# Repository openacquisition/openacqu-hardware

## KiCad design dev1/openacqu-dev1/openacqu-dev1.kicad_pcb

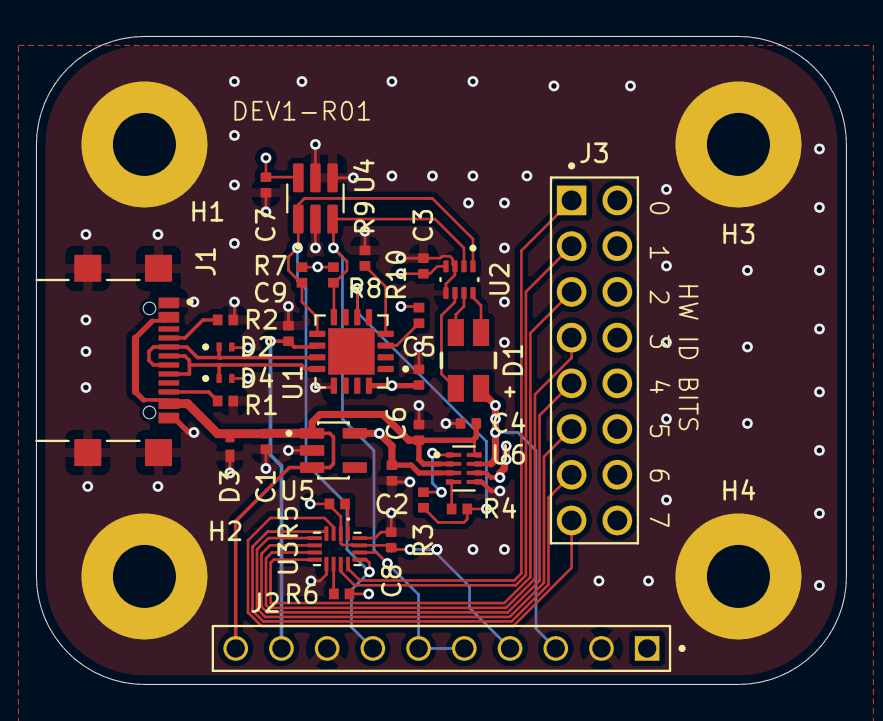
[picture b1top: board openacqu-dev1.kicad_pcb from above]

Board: 4 copper layers, 45.0 x 36.0 mm, 36 parts (0 on the bottom side), 29 nets.

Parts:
C1, C2, C3, C4, C5, C6, C7, C8, C9: 1uF; CAPC1005X55N
D1: 150141M173100; WL-SFTW_3528_PLCC4
D2, D4: ESD321DPYR; TVS_ESD321DPYR
D3: PESD5V0X1UB; SOD523
H1, H2, H3, H4: M3; MountingHole_3.5mm_Pad
J1: GSB1C41110SSHR; AMPHENOL_GSB1C41110SSHR
J2: Test Points; MLE_TSHC-110-S-14-295-G-LF
J3: 77313-118-16LF; AMPHENOL_77313-118-16LF
R1, R2, R7, R8: 5.1k; RESC1005X40N
R3, R4, R5, R6, R9, R10: 10.0k; RESC1005X40N
U1: MCP2221AT-I_ML
U2: LP5817DRLR; IC_LP5817DRLR
U3: FXL6408UMX; QFN40P260X180X55-16N
U4: 24AA025E48T-E_OT; SOT95P270X145-6N
U5: AP2112K-3.3TRG1; SOT95P285X140-5N
U6: TPS22996HQDYCRQ1; IC_TPS22996HQDYCRQ1

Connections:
+3V3: C2.1, C5.1, C9.1, J2.09, R10.1, U1.10 (VUSB), U1.16 (VDD), U5.5 (VOUT), U6.3 (VIN2)
+3V3_SYS: C3.1, C7.1, C8.1, J2.04, J3.02, J3.04, J3.06, J3.08, J3.10, J3.12, J3.14, J3.16, R5.1, R6.1, R7.1, R8.1, U2.4 (VCC), U3.2 (VDDIO), U3.15 (VCC), U4.6 (VCC), U6.6 (VOUT2)
+5V0_SYS: D1.1, J2.03, U6.7 (VOUT1)
/Core/CC1: J1.A5 (CC1), R2.1
/Core/CC2: J1.B5 (CC2), R1.1
/Core/DN: D2.1, J1.A7 (DN1), J1.B7 (DN2), U1.11 (D-)
/Core/DP: D4.1, J1.A6 (DP1), J1.B6 (DP2), U1.12 (D+)
/Core/FX_INT: R5.2, U3.1 (~INT)
/Core/FX_RST: R6.2, U3.10 (~RST)
/Core/LED_B: D1.2, U2.6 (OUT2)
/Core/LED_G: D1.4, U2.7 (OUT1)
/Core/LED_R: D1.3, U2.8 (OUT0)
/Core/MCP_RST: R10.2, U1.3 (~RST)
/Core/MCP_URX: R9.1, U1.4 (URX)
/Core/ON1: R3.2, U6.1 (ON1)
/Core/ON2: R4.2, U6.4 (ON2)
/Core/SCL: J2.07, R7.2, U1.9 (SCL), U2.1 (SCL), U3.13 (SCL), U4.1 (SCL)
/Core/SDA: J2.05, J2.06, R8.2, U1.8 (SDA), U2.2 (SDA), U3.14 (SDA), U4.3 (SDA)
/Core/USBCFG: R3.1, R4.1, U1.6 (GP2)
GND: C1.2, C2.2, C3.2, C4.2, C5.2, C6.2, C7.2, C8.2, C9.2, D2.2, D3.2, D4.2, H1.1, H2.1, H3.1, H4.1, J1.A1_B12 (GND_A), J1.B1_A12 (GND_B), J1.SH1 (SHIELD), J1.SH2 (SHIELD), J1.SH3 (SHIELD), J1.SH4 (SHIELD), J2.02, J2.08, R1.2, R2.2, R9.2, U1.13 (VSS), U2.3 (GND), U2.5 (NC(GND)), U3.9 (ADDR), U3.16 (GND), U4.2 (VSS), U4.4 (A1), U4.5 (A0), U5.2 (GND), U6.5 (GND)
unnamed: J3.01, U3.12 (GPIO0)
unnamed: J3.03, U3.11 (GPIO1)
unnamed: J3.05, U3.8 (GPIO2)
unnamed: J3.07, U3.7 (GPIO3)
unnamed: J3.09, U3.6 (GPIO4)
unnamed: J3.11, U3.5 (GPIO5)
unnamed: J3.13, U3.4 (GPIO6)
unnamed: J3.15, U3.3 (GPIO7)
VBUS: C1.1, C4.1, C6.1, D3.1, J1.A4_B9 (VBUS_A), J1.B4_A9 (VBUS_B), J2.10, U5.1 (VIN), U5.3 (EN), U6.2 (VIN1), U6.8 (VBIAS)

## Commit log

2026-02-03 Added gitignore for KiCAD projects
2026-04-24 Initial commit of the core schematic and library parts
2026-04-24 Core placement and 3D models
2026-04-24 Added .gitignore to allow step files in libraries
2026-04-24 Adding library parts for temp probe
2026-04-26 Routed core design
2026-04-26 Moved core to separate sheet
2026-04-26 Inherited core to tmp1
2026-04-26 Added sensor to tmp1
2026-05-28 Completed layout for the TMP1
2026-05-28 Added stitcing vias
2026-05-29 Updated symbols with JLCPCB part numbers
2026-05-29 Updated 0402 footprint for 100 ohm resistor
2026-05-30 Initial commit of dev board design forked from core
2026-05-30 Placement and routing complete for DEV1
